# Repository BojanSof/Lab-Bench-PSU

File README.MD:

# Programmable laboratory bench power supply

Programmable laboratory bench PSU, consisting of linear regulator and switching
preregulator.

## Block diagram

I used transformer just because I had it laying around.

The switching preregulator is actually buck converter realised with LM2576-ADJ
and it keeps constant 1.5 V on the LDO.

The MCU I used is PIC16F18855, which is very easily available in my country and
it is pretty cheap. It has 10-bit ADC and maximum PWM resolution of 10 bits.

The MCU samples the output, divided by 3 with voltage divider, to obtain the
output voltage value, and the output from the differential amplifier whose 
output is proportional to the voltage of the shunt resistor.

The LDO is realised with TIP41 pass transistor and LM324 operational amplifier
among the main components.

The LCD is 2 rows by 16 columns, with HD44780 controller and the interface to 
the MCU is done via I2C I/O expander (PCF8574).

## Goal specifications

Voltage: 0 - 15 V, with steps of 15 mV
Current: 0 - 1 A, with steps of 5 mA

Additional software modifications and testing is required to meet these 
specifications, especially the current limit one.

## PCB and schematic

The schematic and PCB design is created in KiCad.

The PCB is single layer because I made it in my home. I only used THT
components for the whole design.

## Firmware

The firmware is developed using MPLAB X IDE, with the free version of the XC8 
compiler.

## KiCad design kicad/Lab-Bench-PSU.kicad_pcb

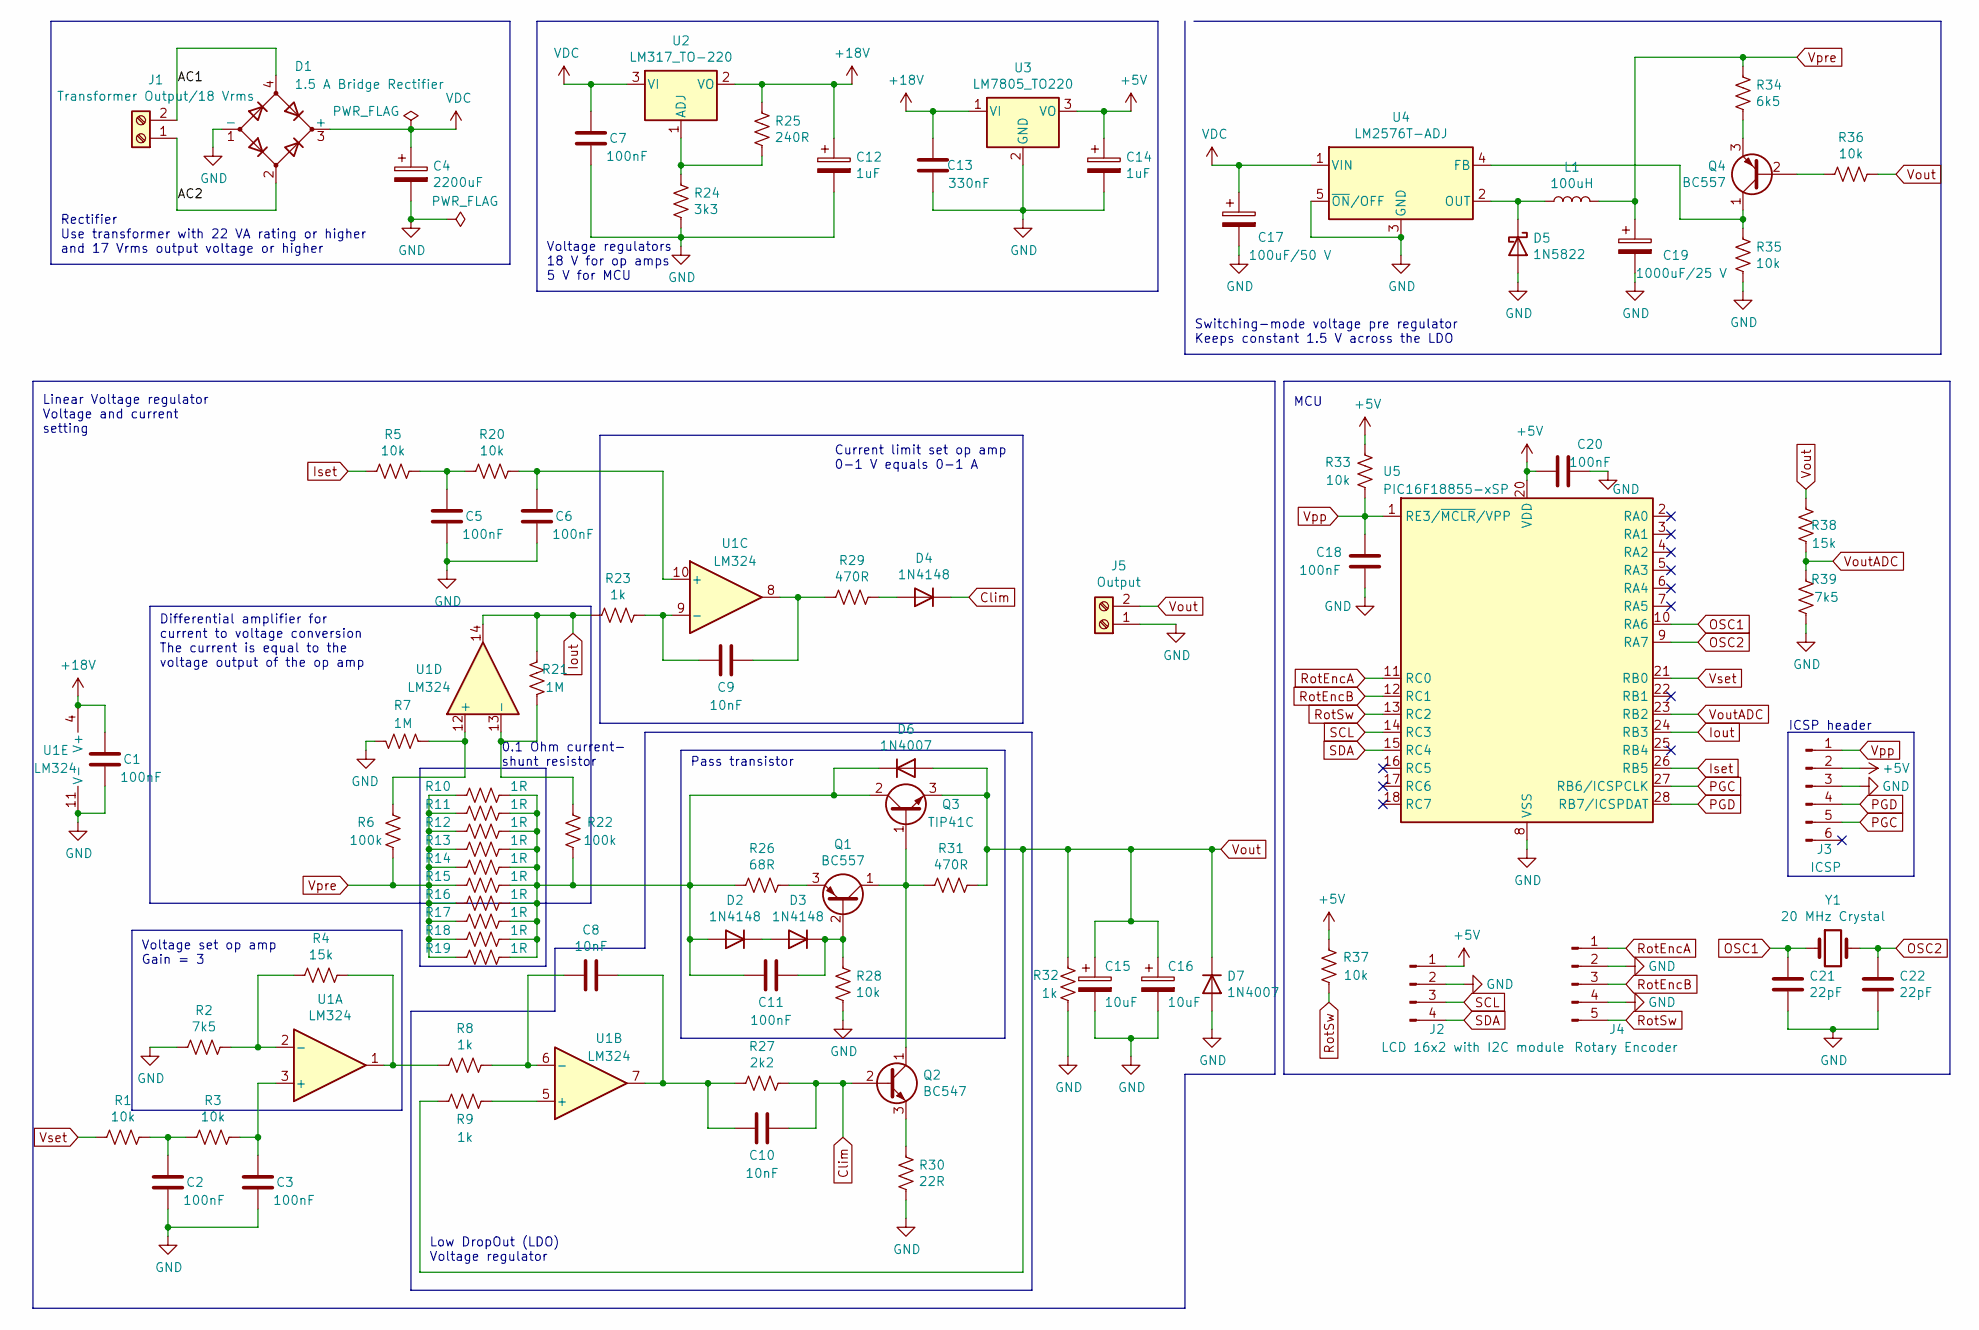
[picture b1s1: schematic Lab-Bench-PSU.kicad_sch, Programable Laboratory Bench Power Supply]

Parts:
C1, C2, C3, C5, C6, C7, C11, C18, C20: 100nF; C_Rect_L7.0mm_W2.5mm_P5.00mm
C4: 2200uF; CP_Radial_D16.0mm_P7.50mm
C8, C9, C10: 10nF; C_Disc_D5.0mm_W2.5mm_P5.00mm
C12, C14: 1uF; CP_Radial_D5.0mm_P2.50mm
C13: 330nF; C_Rect_L7.0mm_W4.5mm_P5.00mm
C15, C16: 10uF; CP_Radial_D5.0mm_P2.50mm
C17: 100uF/50 V; CP_Radial_D10.0mm_P5.00mm
C19: 1000uF/25 V; CP_Radial_D10.0mm_P5.00mm
C21, C22: 22pF; C_Disc_D5.0mm_W2.5mm_P5.00mm
D1: 1.5 A Bridge Rectifier; Diode_Bridge_Round_D9.0mm
D2, D3, D4: 1N4148; D_DO-35_SOD27_P7.62mm_Horizontal
D5: 1N5822; D_DO-201AD_P15.24mm_Horizontal
D6, D7: 1N4007; D_DO-41_SOD81_P10.16mm_Horizontal
J1: Transformer Output/18 Vrms; SolderWire-1.5sqmm_1x02_P6mm_D1.7mm_OD3mm
J2: LCD 16x2 with I2C module; PinHeader_1x04_P2.54mm_Vertical
J3: ICSP; PinHeader_1x06_P2.54mm_Vertical
J4: Rotary Encoder; PinHeader_1x05_P2.54mm_Vertical
J5: Output; TerminalBlock_Altech_AK300-2_P5.00mm
L1: 100uH; L_Radial_D10.0mm_P5.00mm_Fastron_07M
Q1, Q4: BC557; TO-92_Inline_Wide
Q2: BC547; TO-92_Inline_Wide
Q3: TIP41C; TO-220-3_Vertical
R1, R3, R5, R20, R28, R33, R35, R36, R37: 10k; R_Axial_DIN0207_L6.3mm_D2.5mm_P10.16mm_Horizontal
R2, R39: 7k5; R_Axial_DIN0207_L6.3mm_D2.5mm_P10.16mm_Horizontal
R4, R38: 15k; R_Axial_DIN0207_L6.3mm_D2.5mm_P10.16mm_Horizontal
R6, R22: 100k; R_Axial_DIN0207_L6.3mm_D2.5mm_P10.16mm_Horizontal
R7, R21: 1M; R_Axial_DIN0207_L6.3mm_D2.5mm_P10.16mm_Horizontal
R8, R9, R23, R32: 1k; R_Axial_DIN0207_L6.3mm_D2.5mm_P10.16mm_Horizontal
R10, R11, R12, R13, R14, R15, R16, R17, R18, R19: 1R; R_Axial_DIN0207_L6.3mm_D2.5mm_P10.16mm_Horizontal
R24: 3k3; R_Axial_DIN0207_L6.3mm_D2.5mm_P10.16mm_Horizontal
R25: 240R; R_Axial_DIN0207_L6.3mm_D2.5mm_P10.16mm_Horizontal
R26: 68R; R_Axial_DIN0207_L6.3mm_D2.5mm_P10.16mm_Horizontal
R27: 2k2; R_Axial_DIN0207_L6.3mm_D2.5mm_P10.16mm_Horizontal
R29, R31: 470R; R_Axial_DIN0207_L6.3mm_D2.5mm_P10.16mm_Horizontal
R30: 22R; R_Axial_DIN0207_L6.3mm_D2.5mm_P10.16mm_Horizontal
R34: 6k5; R_Axial_DIN0207_L6.3mm_D2.5mm_P10.16mm_Horizontal
U1: LM324; DIP-14_W7.62mm_LongPads
U2: LM317_TO-220; TO-220-3_Vertical
U3: LM7805_TO220; TO-220-3_Vertical
U4: LM2576T-ADJ; TO-220-5_Vertical
U5: PIC16F18855-xSP; DIP-28_W7.62mm_LongPads
Y1: 20 MHz Crystal; Crystal_HC18-U_Vertical

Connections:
+5V: C14.1, C20.1, J2.1, J3.2, R33.2, R37.2, U3.3 (VO), U5.20 (VDD)
+18V: C1.1, C12.1, C13.1, R25.1, U1.4 (V+), U2.2 (VO), U3.1 (VI)
/AC1: D1.4, J1.2
/AC2: D1.2, J1.1
Clim: C10.1, D4.1 (K), Q2.2 (B), R27.1
GND: C1.2, C2.2, C3.2, C4.2, C5.2, C6.2, C7.2, C12.2, C13.2, C14.2, C15.2, C16.2, C17.2, C18.2, C19.2, C20.2, C21.2, C22.2, D1.1 (-), D5.2 (A), D7.2 (A), J2.2, J3.3, J4.2, J4.4, J5.1, R2.2, R7.1, R24.2, R28.1, R30.1, R32.1, R35.1, R39.1, U1.11 (V-), U3.2 (GND), U4.3 (GND), U4.5 (~ON/OFF), U5.8 (VSS), U5.19 (VSS)
Iout: R21.2, R23.1, U1.14, U5.24 (RB3)
Iset: R5.1, U5.26 (RB5)
unnamed: C2.1, R1.2, R3.1
unnamed: C3.1, R3.2, U1.3 (+)
unnamed: C5.1, R5.2, R20.1
unnamed: C6.1, R20.2, U1.10 (+)
unnamed: C8.2, R8.1, U1.6 (-)
unnamed: C9.1, R29.2, U1.8
unnamed: C9.2, R23.2, U1.9 (-)
unnamed: C8.1, C10.2, R27.2, U1.7
unnamed: C11.1, D3.1 (K), Q1.2 (B), R28.2
unnamed: C11.2, D2.2 (A), D6.1 (K), Q3.2 (C), R10.1, R11.1, R12.1, R13.1, R14.1, R15.1, R16.1, R17.1, R18.1, R19.1, R22.1, R26.2
unnamed: D2.1 (K), D3.2 (A)
unnamed: D4.2 (A), R29.1
unnamed: D5.1 (K), L1.1, U4.2 (OUT)
unnamed: Q1.1 (C), Q2.1 (C), Q3.1 (B), R31.2
unnamed: Q1.3 (E), R26.1
unnamed: Q2.3 (E), R30.2
unnamed: Q4.1 (C), R35.2, U4.4 (FB)
unnamed: Q4.2 (B), R36.1
unnamed: Q4.3 (E), R34.1
unnamed: R2.1, R4.2, U1.2 (-)
unnamed: R4.1, R8.2, U1.1
unnamed: R6.2, R7.2, U1.12 (+)
unnamed: R9.1, U1.5 (+)
unnamed: R21.1, R22.2, U1.13 (-)
unnamed: R24.1, R25.2, U2.1 (ADJ)
OSC1: C21.1, U5.10 (RA6), Y1.1
OSC2: C22.1, U5.9 (RA7), Y1.2
PGC: J3.5, U5.27 (RB6/ICSPCLK)
PGD: J3.4, U5.28 (RB7/ICSPDAT)
RotEncA: J4.1, U5.11 (RC0)
RotEncB: J4.3, U5.12 (RC1)
RotSw: J4.5, R37.1, U5.13 (RC2)
SCL: J2.3, U5.14 (RC3)
SDA: J2.4, U5.15 (RC4)
VDC: C4.1, C7.1, C17.1, D1.3 (+), U2.3 (VI), U4.1 (VIN)
Vout: C15.1, C16.1, D6.2 (A), D7.1 (K), J5.2, Q3.3 (E), R9.2, R31.1, R32.2, R36.2, R38.2
VoutADC: R38.1, R39.2, U5.23 (RB2)
Vpp: C18.1, J3.1, R33.1, U5.1 (RE3/~MCLR/VPP)
Vpre: C19.1, L1.2, R6.1, R10.2, R11.2, R12.2, R13.2, R14.2, R15.2, R16.2, R17.2, R18.2, R19.2, R34.2
Vset: R1.1, U5.21 (RB0)

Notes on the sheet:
ICSP header
Low DropOut (LDO) Voltage regulator
MCU
Voltage regulators 18 V for op amps 5 V for MCU
Switching-mode voltage pre regulator Keeps constant 1.5 V across the LDO
Rectifier Use transformer with 22 VA rating or higher and 17 Vrms output voltage or higher
0.1 Ohm current- shunt resistor
Pass transistor
Linear Voltage regulator Voltage and current setting
Current limit set op amp 0-1 V equals 0-1 A
Voltage set op amp Gain = 3
Differential amplifier for current to voltage conversion The current is equal to the voltage output of the op amp

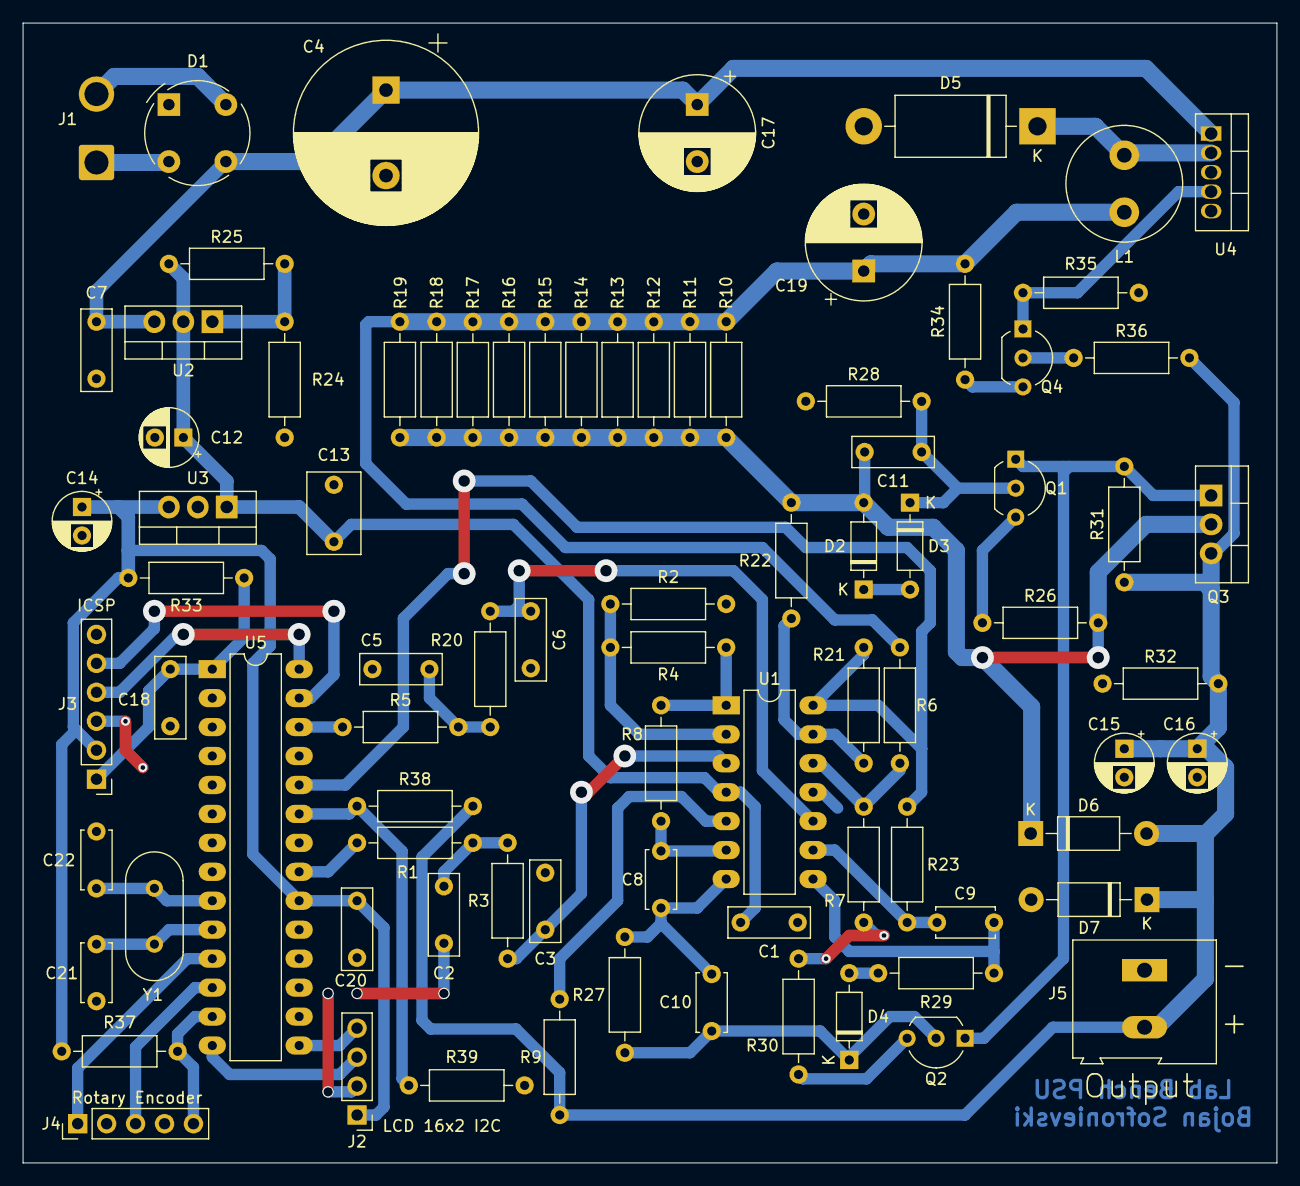
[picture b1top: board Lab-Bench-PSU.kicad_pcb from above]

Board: 2 copper layers, 110.0 x 100.0 mm, 84 parts (0 on the bottom side), 48 nets.

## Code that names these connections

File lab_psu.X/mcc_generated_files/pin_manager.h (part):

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#define RB0_SetHigh()            do { LATBbits.LATB0 = 1; } while(0)
#define RB0_SetLow()             do { LATBbits.LATB0 = 0; } while(0)
#define RB0_Toggle()             do { LATBbits.LATB0 = ~LATBbits.LATB0; } while(0)
#define RB0_GetValue()              PORTBbits.RB0
#define RB0_SetDigitalInput()    do { TRISBbits.TRISB0 = 1; } while(0)
#define RB0_SetDigitalOutput()   do { TRISBbits.TRISB0 = 0; } while(0)
#define RB0_SetPullup()             do { WPUBbits.WPUB0 = 1; } while(0)
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// get/set Vout aliases
#define Vout_TRIS                 TRISBbits.TRISB2
#define Vout_LAT                  LATBbits.LATB2
#define Vout_PORT                 PORTBbits.RB2
#define Vout_WPU                  WPUBbits.WPUB2
#define Vout_OD                   ODCONBbits.ODCB2
#define Vout_ANS                  ANSELBbits.ANSB2
#define Vout_SetHigh()            do { LATBbits.LATB2 = 1; } while(0)
#define Vout_SetLow()             do { LATBbits.LATB2 = 0; } while(0)
#define Vout_Toggle()             do { LATBbits.LATB2 = ~LATBbits.LATB2; } while(0)
#define Vout_GetValue()           PORTBbits.RB2
#define Vout_SetDigitalInput()    do { TRISBbits.TRISB2 = 1; } while(0)
#define Vout_SetDigitalOutput()   do { TRISBbits.TRISB2 = 0; } while(0)
#define Vout_SetPullup()          do { WPUBbits.WPUB2 = 1; } while(0)
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// get/set Iout aliases
#define Iout_TRIS                 TRISBbits.TRISB3
#define Iout_LAT                  LATBbits.LATB3
#define Iout_PORT                 PORTBbits.RB3
#define Iout_WPU                  WPUBbits.WPUB3
#define Iout_OD                   ODCONBbits.ODCB3
#define Iout_ANS                  ANSELBbits.ANSB3
#define Iout_SetHigh()            do { LATBbits.LATB3 = 1; } while(0)
#define Iout_SetLow()             do { LATBbits.LATB3 = 0; } while(0)
#define Iout_Toggle()             do { LATBbits.LATB3 = ~LATBbits.LATB3; } while(0)
#define Iout_GetValue()           PORTBbits.RB3
#define Iout_SetDigitalInput()    do { TRISBbits.TRISB3 = 1; } while(0)
#define Iout_SetDigitalOutput()   do { TRISBbits.TRISB3 = 0; } while(0)
#define Iout_SetPullup()          do { WPUBbits.WPUB3 = 1; } while(0)
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#define RB5_SetHigh()            do { LATBbits.LATB5 = 1; } while(0)
#define RB5_SetLow()             do { LATBbits.LATB5 = 0; } while(0)
#define RB5_Toggle()             do { LATBbits.LATB5 = ~LATBbits.LATB5; } while(0)
#define RB5_GetValue()              PORTBbits.RB5
#define RB5_SetDigitalInput()    do { TRISBbits.TRISB5 = 1; } while(0)
#define RB5_SetDigitalOutput()   do { TRISBbits.TRISB5 = 0; } while(0)
#define RB5_SetPullup()             do { WPUBbits.WPUB5 = 1; } while(0)
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// get/set RotEncCLK aliases
#define RotEncCLK_TRIS                 TRISCbits.TRISC0
#define RotEncCLK_LAT                  LATCbits.LATC0
#define RotEncCLK_PORT                 PORTCbits.RC0
#define RotEncCLK_WPU                  WPUCbits.WPUC0
#define RotEncCLK_OD                   ODCONCbits.ODCC0
#define RotEncCLK_ANS                  ANSELCbits.ANSC0
#define RotEncCLK_SetHigh()            do { LATCbits.LATC0 = 1; } while(0)
#define RotEncCLK_SetLow()             do { LATCbits.LATC0 = 0; } while(0)
#define RotEncCLK_Toggle()             do { LATCbits.LATC0 = ~LATCbits.LATC0; } while(0)
#define RotEncCLK_GetValue()           PORTCbits.RC0
#define RotEncCLK_SetDigitalInput()    do { TRISCbits.TRISC0 = 1; } while(0)
#define RotEncCLK_SetDigitalOutput()   do { TRISCbits.TRISC0 = 0; } while(0)
#define RotEncCLK_SetPullup()          do { WPUCbits.WPUC0 = 1; } while(0)
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// get/set RotEncDT aliases
#define RotEncDT_TRIS                 TRISCbits.TRISC1
#define RotEncDT_LAT                  LATCbits.LATC1
#define RotEncDT_PORT                 PORTCbits.RC1
#define RotEncDT_WPU                  WPUCbits.WPUC1
#define RotEncDT_OD                   ODCONCbits.ODCC1
#define RotEncDT_ANS                  ANSELCbits.ANSC1
#define RotEncDT_SetHigh()            do { LATCbits.LATC1 = 1; } while(0)
#define RotEncDT_SetLow()             do { LATCbits.LATC1 = 0; } while(0)
#define RotEncDT_Toggle()             do { LATCbits.LATC1 = ~LATCbits.LATC1; } while(0)
#define RotEncDT_GetValue()           PORTCbits.RC1
#define RotEncDT_SetDigitalInput()    do { TRISCbits.TRISC1 = 1; } while(0)
#define RotEncDT_SetDigitalOutput()   do { TRISCbits.TRISC1 = 0; } while(0)
#define RotEncDT_SetPullup()          do { WPUCbits.WPUC1 = 1; } while(0)
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// get/set RotEncSW aliases
#define RotEncSW_TRIS                 TRISCbits.TRISC2
#define RotEncSW_LAT                  LATCbits.LATC2
#define RotEncSW_PORT                 PORTCbits.RC2
#define RotEncSW_WPU                  WPUCbits.WPUC2
#define RotEncSW_OD                   ODCONCbits.ODCC2
#define RotEncSW_ANS                  ANSELCbits.ANSC2
#define RotEncSW_SetHigh()            do { LATCbits.LATC2 = 1; } while(0)
#define RotEncSW_SetLow()             do { LATCbits.LATC2 = 0; } while(0)
#define RotEncSW_Toggle()             do { LATCbits.LATC2 = ~LATCbits.LATC2; } while(0)
#define RotEncSW_GetValue()           PORTCbits.RC2
#define RotEncSW_SetDigitalInput()    do { TRISCbits.TRISC2 = 1; } while(0)
#define RotEncSW_SetDigitalOutput()   do { TRISCbits.TRISC2 = 0; } while(0)
#define RotEncSW_SetPullup()          do { WPUCbits.WPUC2 = 1; } while(0)
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#define RC3_SetHigh()            do { LATCbits.LATC3 = 1; } while(0)
#define RC3_SetLow()             do { LATCbits.LATC3 = 0; } while(0)
#define RC3_Toggle()             do { LATCbits.LATC3 = ~LATCbits.LATC3; } while(0)
#define RC3_GetValue()              PORTCbits.RC3
#define RC3_SetDigitalInput()    do { TRISCbits.TRISC3 = 1; } while(0)
#define RC3_SetDigitalOutput()   do { TRISCbits.TRISC3 = 0; } while(0)
#define RC3_SetPullup()             do { WPUCbits.WPUC3 = 1; } while(0)
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#define RC4_SetHigh()            do { LATCbits.LATC4 = 1; } while(0)
#define RC4_SetLow()             do { LATCbits.LATC4 = 0; } while(0)
#define RC4_Toggle()             do { LATCbits.LATC4 = ~LATCbits.LATC4; } while(0)
#define RC4_GetValue()              PORTCbits.RC4
#define RC4_SetDigitalInput()    do { TRISCbits.TRISC4 = 1; } while(0)
#define RC4_SetDigitalOutput()   do { TRISCbits.TRISC4 = 0; } while(0)
#define RC4_SetPullup()             do { WPUCbits.WPUC4 = 1; } while(0)
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

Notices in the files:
lab_psu.X/mcc_generated_files/pin_manager.h:
(c) 2018 Microchip Technology Inc. and its subsidiaries.
